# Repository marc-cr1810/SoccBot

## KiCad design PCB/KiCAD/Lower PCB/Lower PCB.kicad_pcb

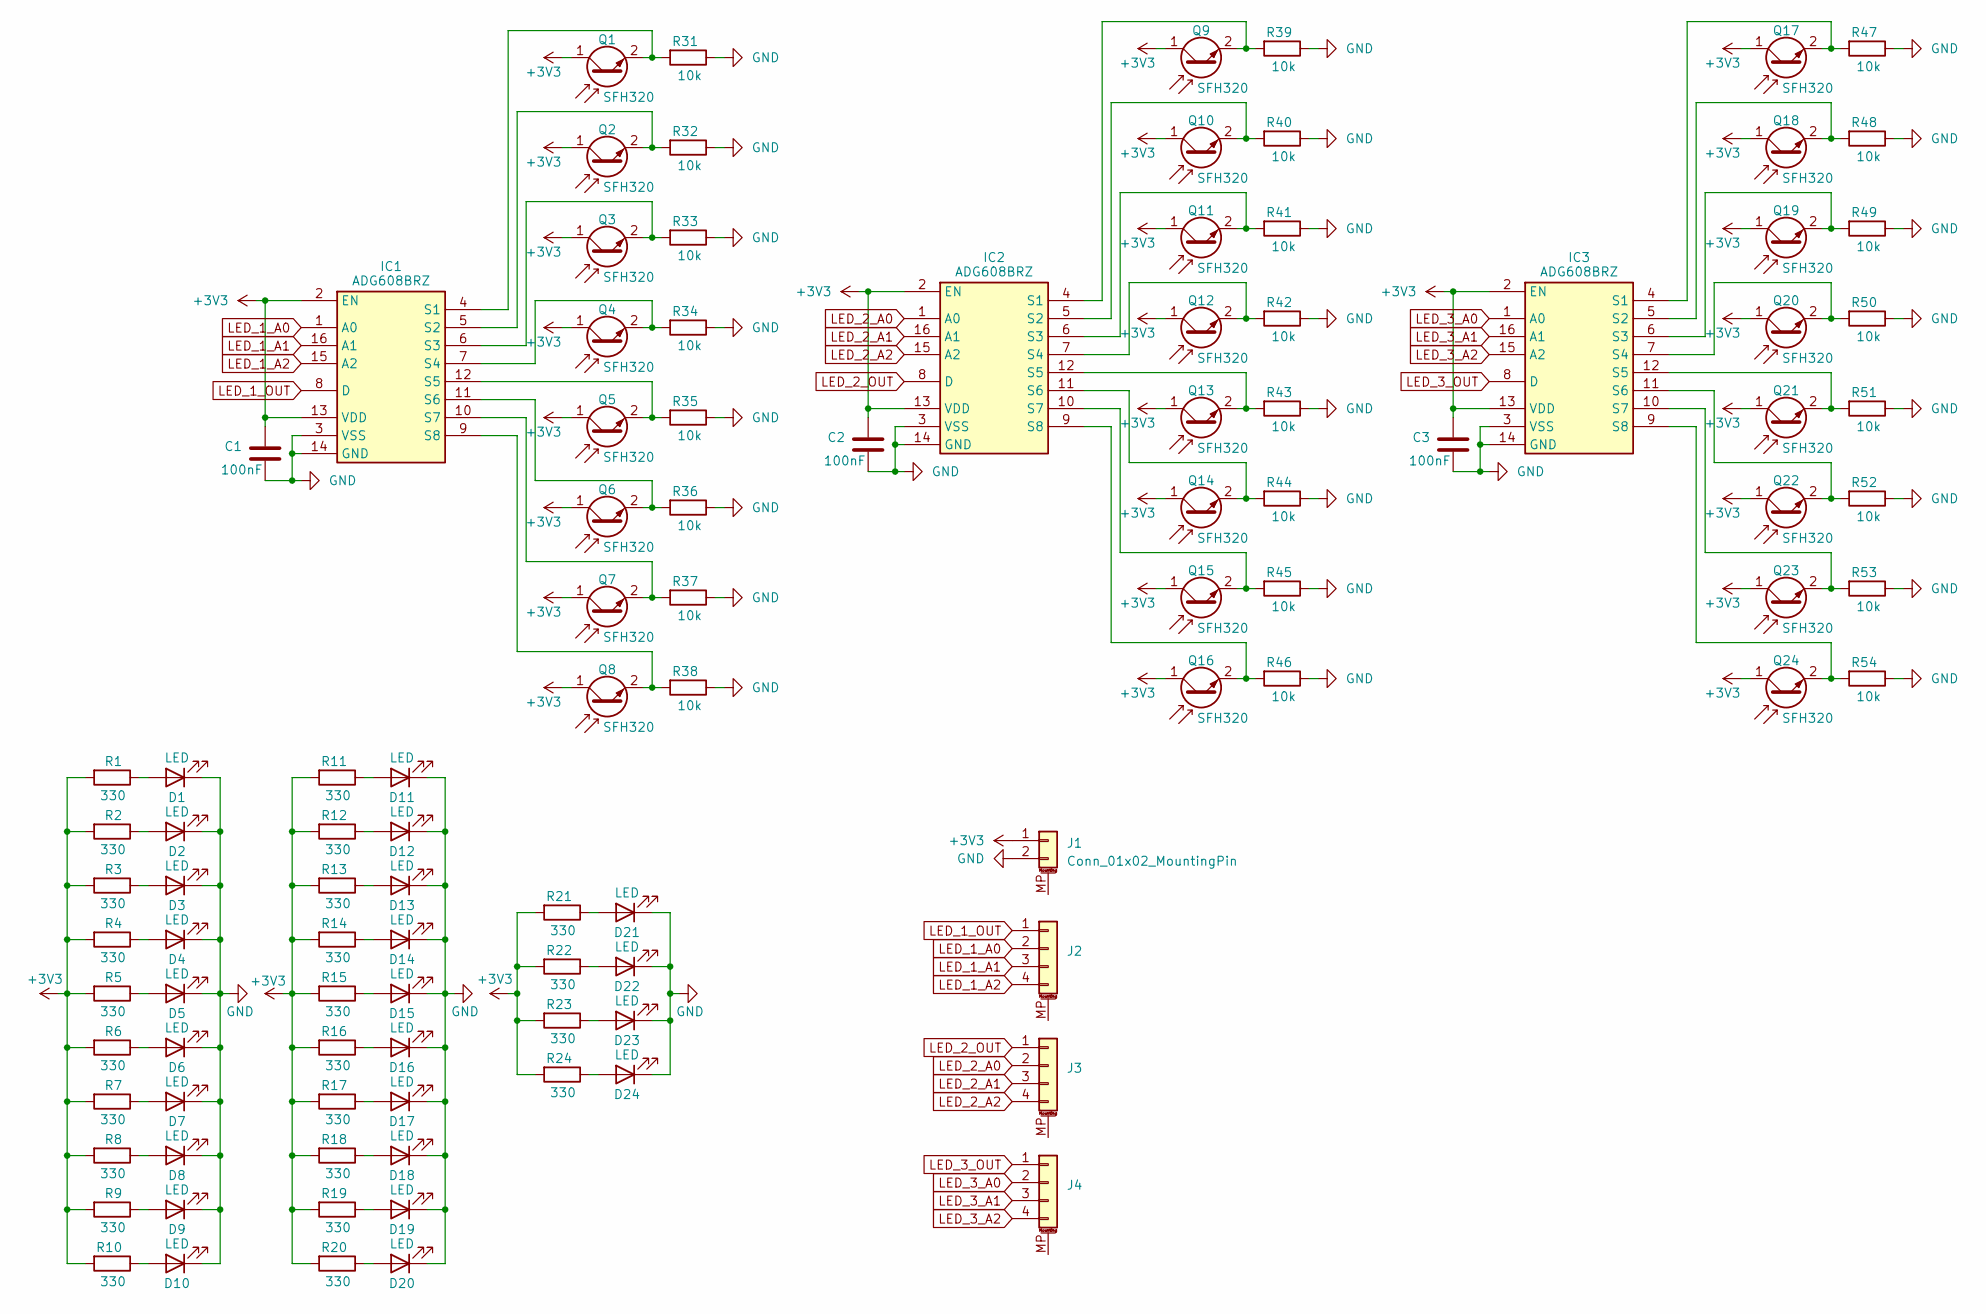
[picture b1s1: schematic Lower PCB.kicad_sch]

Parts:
C1, C2, C3: 100nF; C_0805_2012Metric_Pad1.18x1.45mm_HandSolder
D1, D2, D3, D4, D5, D6, D7, D8, D9, D10, D11, D12, D13, D14, D15, D16, D17, D18, D19, D20, D21, D22, D23, D24: LED; LED_PLCC-2_3.4x3.0mm_KA
IC1, IC2, IC3: ADG608BRZ; SOIC127P600X175-16N; Mouser Part Number 584-ADG608BRZ
J1: Conn_01x02_MountingPin; JST_PH_S2B-PH-SM4-TB_1x02-1MP_P2.00mm_Horizontal
J2, J3, J4: Conn_01x04_MountingPin; JST_PH_S4B-PH-SM4-TB_1x04-1MP_P2.00mm_Horizontal
Q1, Q2, Q3, Q4, Q5, Q6, Q7, Q8, Q9, Q10, Q11, Q12, Q13, Q14, Q15, Q16, Q17, Q18, Q19, Q20, Q21, Q22, Q23, Q24: SFH320; LED_PLCC-2_3.4x3.0mm_KA
R1, R2, R3, R4, R5, R6, R7, R8, R9, R10, R11, R12, R13, R14, R15, R16, R17, R18, R19, R20, R21, R22, R23, R24: 330; R_0805_2012Metric_Pad1.20x1.40mm_HandSolder
R31, R32, R33, R34, R35, R36, R37, R38, R39, R40, R41, R42, R43, R44, R45, R46, R47, R48, R49, R50, R51, R52, R53, R54: 10k; R_0805_2012Metric_Pad1.20x1.40mm_HandSolder

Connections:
+3V3: C1.1, C2.1, C3.1, IC1.2 (EN), IC1.13 (VDD), IC2.2 (EN), IC2.13 (VDD), IC3.2 (EN), IC3.13 (VDD), J1.1, Q1.1 (C), Q2.1 (C), Q3.1 (C), Q4.1 (C), Q5.1 (C), Q6.1 (C), Q7.1 (C), Q8.1 (C), Q9.1 (C), Q10.1 (C), Q11.1 (C), Q12.1 (C), Q13.1 (C), Q14.1 (C), Q15.1 (C), Q16.1 (C), Q17.1 (C), Q18.1 (C), Q19.1 (C), Q20.1 (C), Q21.1 (C), Q22.1 (C), Q23.1 (C), Q24.1 (C), R1.2, R2.2, R3.2, R4.2, R5.2, R6.2, R7.2, R8.2, R9.2, R10.2, R11.2, R12.2, R13.2, R14.2, R15.2, R16.2, R17.2, R18.2, R19.2, R20.2, R21.2, R22.2, R23.2, R24.2
GND: C1.2, C2.2, C3.2, D1.1 (K), D2.1 (K), D3.1 (K), D4.1 (K), D5.1 (K), D6.1 (K), D7.1 (K), D8.1 (K), D9.1 (K), D10.1 (K), D11.1 (K), D12.1 (K), D13.1 (K), D14.1 (K), D15.1 (K), D16.1 (K), D17.1 (K), D18.1 (K), D19.1 (K), D20.1 (K), D21.1 (K), D22.1 (K), D23.1 (K), D24.1 (K), IC1.3 (VSS), IC1.14 (GND), IC2.3 (VSS), IC2.14 (GND), IC3.3 (VSS), IC3.14 (GND), J1.2, R31.1, R32.1, R33.1, R34.1, R35.1, R36.1, R37.1, R38.1, R39.1, R40.1, R41.1, R42.1, R43.1, R44.1, R45.1, R46.1, R47.1, R48.1, R49.1, R50.1, R51.1, R52.1, R53.1, R54.1
LED_1_A0: IC1.1 (A0), J2.2
LED_1_A1: IC1.16 (A1), J2.3
LED_1_A2: IC1.15 (A2), J2.4
LED_1_OUT: IC1.8 (D), J2.1
LED_2_A0: IC2.1 (A0), J3.2
LED_2_A1: IC2.16 (A1), J3.3
LED_2_A2: IC2.15 (A2), J3.4
LED_2_OUT: IC2.8 (D), J3.1
LED_3_A0: IC3.1 (A0), J4.2
LED_3_A1: IC3.16 (A1), J4.3
LED_3_A2: IC3.15 (A2), J4.4
LED_3_OUT: IC3.8 (D), J4.1
unnamed: D1.2 (A), R1.1
unnamed: D2.2 (A), R2.1
unnamed: D3.2 (A), R3.1
unnamed: D4.2 (A), R4.1
unnamed: D5.2 (A), R5.1
unnamed: D6.2 (A), R6.1
unnamed: D7.2 (A), R7.1
unnamed: D8.2 (A), R8.1
unnamed: D9.2 (A), R9.1
unnamed: D10.2 (A), R10.1
unnamed: D11.2 (A), R11.1
unnamed: D12.2 (A), R12.1
unnamed: D13.2 (A), R13.1
unnamed: D14.2 (A), R14.1
unnamed: D15.2 (A), R15.1
unnamed: D16.2 (A), R16.1
unnamed: D17.2 (A), R17.1
unnamed: D18.2 (A), R18.1
unnamed: D19.2 (A), R19.1
unnamed: D20.2 (A), R20.1
unnamed: D21.2 (A), R21.1
unnamed: D22.2 (A), R22.1
unnamed: D23.2 (A), R23.1
unnamed: D24.2 (A), R24.1
unnamed: IC1.4 (S1), Q1.2 (E), R31.2
unnamed: IC1.5 (S2), Q2.2 (E), R32.2
unnamed: IC1.6 (S3), Q3.2 (E), R33.2
unnamed: IC1.7 (S4), Q4.2 (E), R34.2
unnamed: IC1.12 (S5), Q5.2 (E), R35.2
unnamed: IC1.11 (S6), Q6.2 (E), R36.2
unnamed: IC1.10 (S7), Q7.2 (E), R37.2
unnamed: IC1.9 (S8), Q8.2 (E), R38.2
unnamed: IC2.4 (S1), Q9.2 (E), R39.2
unnamed: IC2.5 (S2), Q10.2 (E), R40.2
unnamed: IC2.6 (S3), Q11.2 (E), R41.2
unnamed: IC2.7 (S4), Q12.2 (E), R42.2
unnamed: IC2.12 (S5), Q13.2 (E), R43.2
unnamed: IC2.11 (S6), Q14.2 (E), R44.2
unnamed: IC2.10 (S7), Q15.2 (E), R45.2
unnamed: IC2.9 (S8), Q16.2 (E), R46.2
unnamed: IC3.4 (S1), Q17.2 (E), R47.2
unnamed: IC3.5 (S2), Q18.2 (E), R48.2
unnamed: IC3.6 (S3), Q19.2 (E), R49.2
unnamed: IC3.7 (S4), Q20.2 (E), R50.2
unnamed: IC3.12 (S5), Q21.2 (E), R51.2
unnamed: IC3.11 (S6), Q22.2 (E), R52.2
unnamed: IC3.10 (S7), Q23.2 (E), R53.2
unnamed: IC3.9 (S8), Q24.2 (E), R54.2

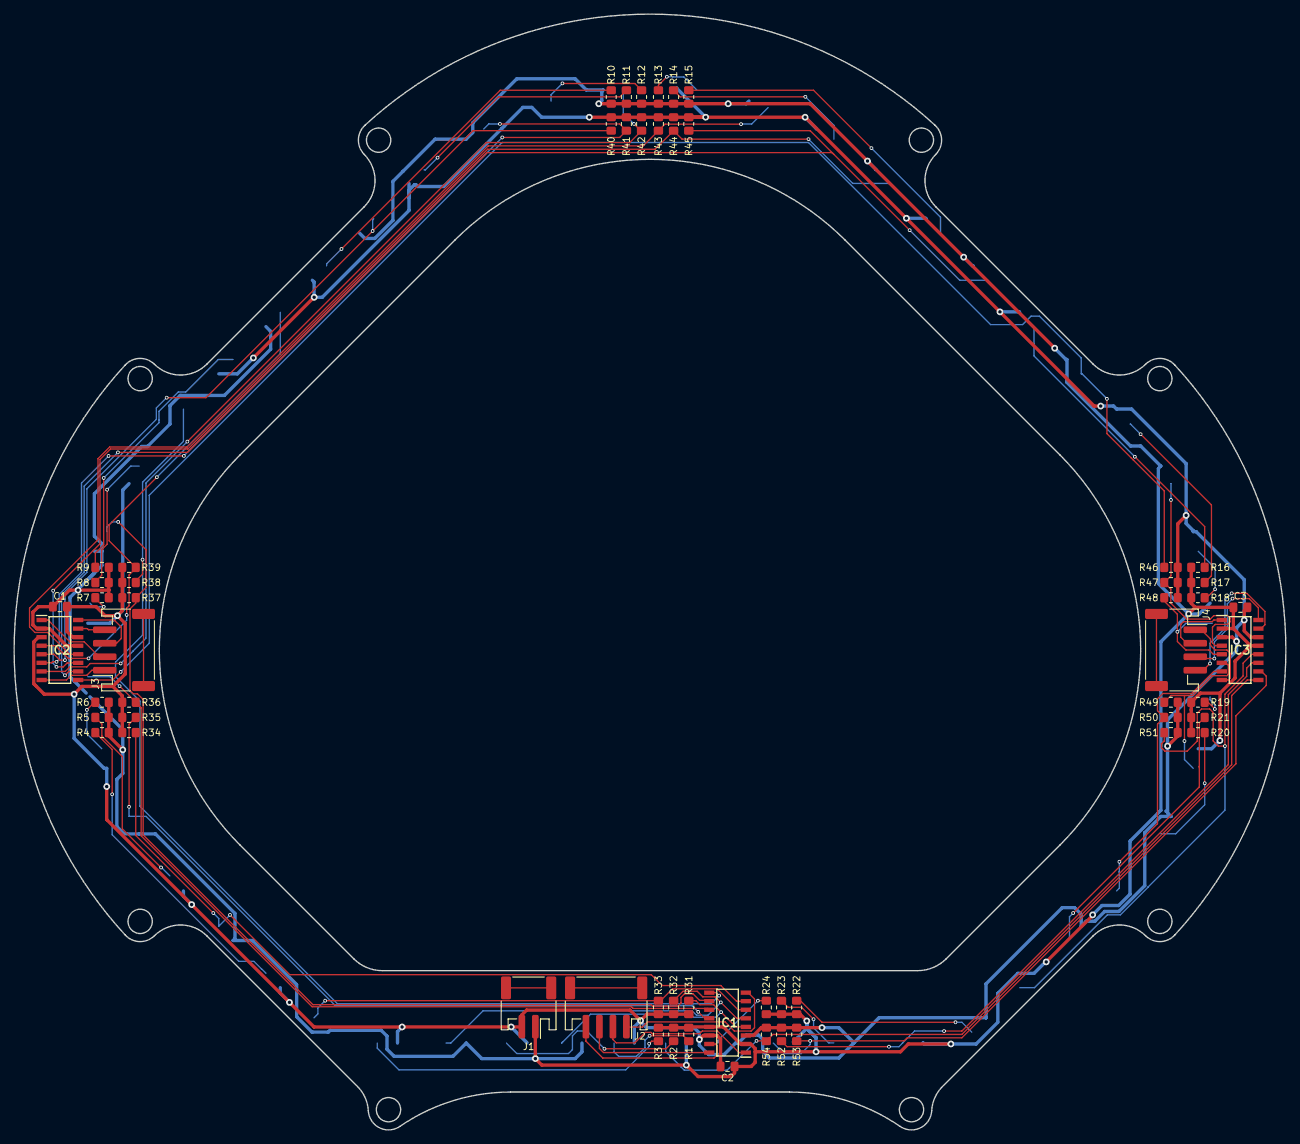
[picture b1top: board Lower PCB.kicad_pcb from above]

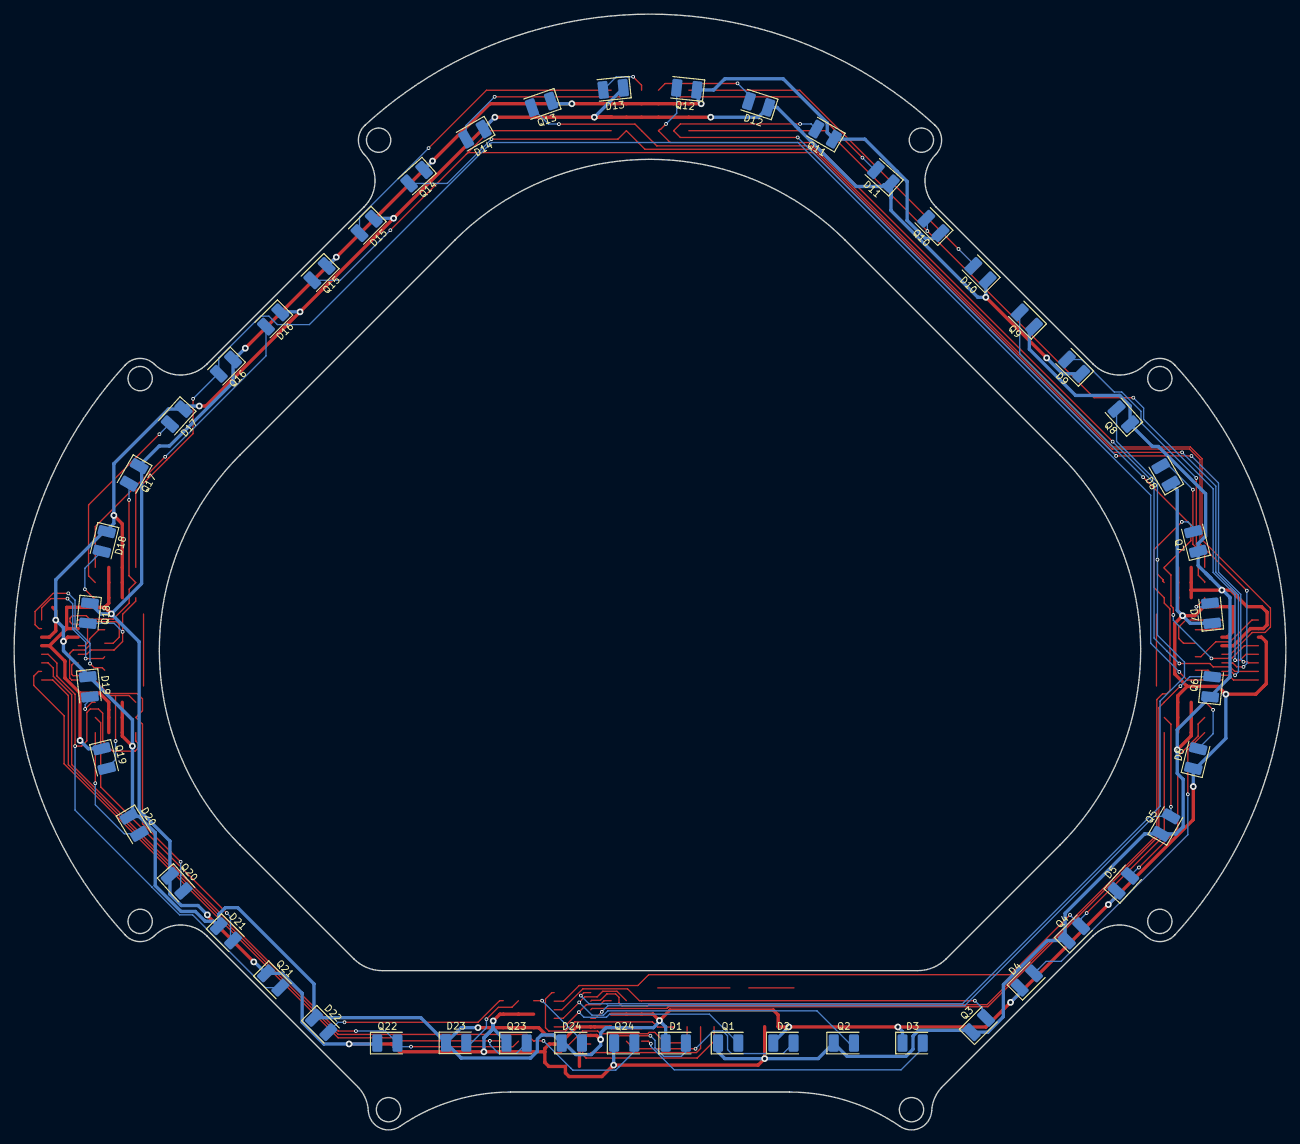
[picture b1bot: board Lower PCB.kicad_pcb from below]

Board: 2 copper layers, 188.6 x 165.4 mm, 106 parts (48 on the bottom side), 62 nets.

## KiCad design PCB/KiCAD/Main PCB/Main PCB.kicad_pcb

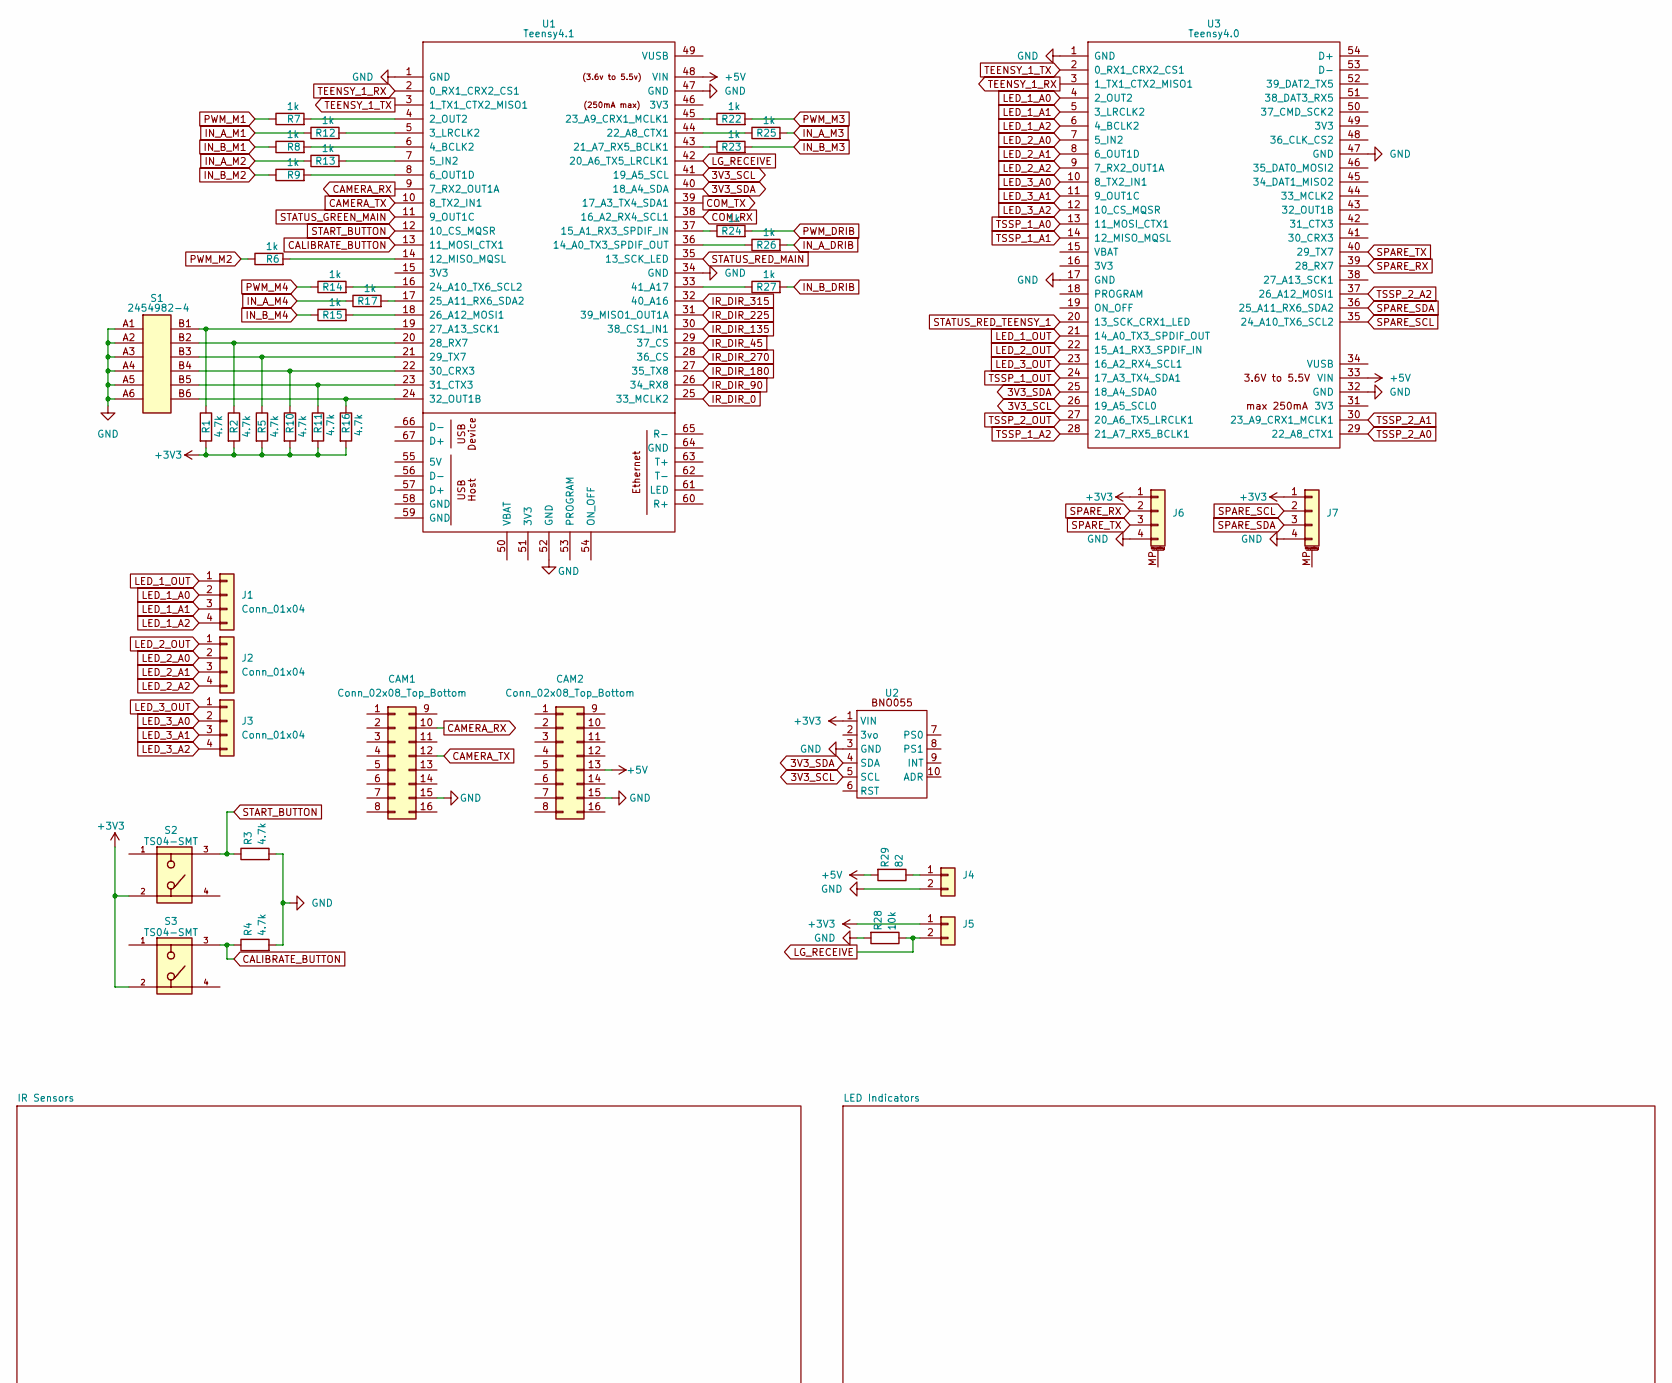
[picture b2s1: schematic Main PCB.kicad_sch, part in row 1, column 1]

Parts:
CAM1, CAM2: Conn_02x08_Top_Bottom; PinSocket_2x08_P2.54mm_Vertical
J1, J2, J3: Conn_01x04; JST_PH_B4B-PH-K_1x04_P2.00mm_Vertical
J4, J5: Conn_01x02; JST_PH_B2B-PH-K_1x02_P2.00mm_Vertical
J6, J7: Conn_01x04_MountingPin; JST_PH_S4B-PH-SM4-TB_1x04-1MP_P2.00mm_Horizontal
R1, R2, R3, R4, R5, R10, R11, R16: 4.7k; R_0805_2012Metric_Pad1.20x1.40mm_HandSolder
R6, R7, R8, R9, R12, R13, R14, R15, R17, R22, R23, R24, R25, R26, R27: 1k; R_0805_2012Metric_Pad1.20x1.40mm_HandSolder
R28: 10k; R_0805_2012Metric_Pad1.20x1.40mm_HandSolder
R29: 82; R_0805_2012Metric_Pad1.20x1.40mm_HandSolder
S1: 2454982-4; DIP_6_SWITCH_THT; Mouser Part Number 655-2454982-4
S2, S3: TS04-SMT; SW_TS04-66-70-BK-260-SMT; PARTREV 1.0
U1: Teensy4.1; Teensy41
U2: BNO055
U3: Teensy4.0; Teensy40

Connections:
3V3_SCL: U1.41 (19_A5_SCL), U2.5 (SCL), U3.26 (19_A5_SCL0)
3V3_SDA: U1.40 (18_A4_SDA), U2.4 (SDA), U3.25 (18_A4_SDA0)
+3V3: J5.1, J6.1, J7.1, R1.2, R2.2, R5.2, R10.2, R11.2, R16.2, S2.2, S3.2, U2.1 (VIN); also elsewhere on the board
+5V: CAM2.13, R29.2, U1.48 (VIN), U3.33 (VIN); also elsewhere on the board
CALIBRATE_BUTTON: R4.1, S3.3, U1.13 (11_MOSI_CTX1)
CAMERA_RX: CAM1.10, U1.9 (7_RX2_OUT1A)
CAMERA_TX: CAM1.12, U1.10 (8_TX2_IN1)
COM_RX: U1.38 (16_A2_RX4_SCL1); also elsewhere on the board
COM_TX: U1.39 (17_A3_TX4_SDA1); also elsewhere on the board
GND: CAM1.15, CAM2.15, J4.2, J6.4, J7.4, R3.2, R4.2, R28.2, S1.A1, S1.A2, S1.A3, S1.A4, S1.A5, S1.A6, U1.1 (GND), U1.34 (GND), U1.47 (GND), U1.52 (GND), U2.3 (GND), U3.1 (GND), U3.17 (GND), U3.32 (GND), U3.47 (GND); also elsewhere on the board
IN_A_DRIB: R26.2; also elsewhere on the board
IN_A_M1: R12.1; also elsewhere on the board
IN_A_M2: R13.1; also elsewhere on the board
IN_A_M3: R25.2; also elsewhere on the board
IN_A_M4: R17.1; also elsewhere on the board
IN_B_DRIB: R27.2; also elsewhere on the board
IN_B_M1: R8.1; also elsewhere on the board
IN_B_M2: R9.1; also elsewhere on the board
IN_B_M3: R23.2; also elsewhere on the board
IN_B_M4: R15.1; also elsewhere on the board
IR_DIR_0: U1.25 (33_MCLK2); also elsewhere on the board
IR_DIR_45: U1.29 (37_CS); also elsewhere on the board
IR_DIR_90: U1.26 (34_RX8); also elsewhere on the board
IR_DIR_135: U1.30 (38_CS1_IN1); also elsewhere on the board
IR_DIR_180: U1.27 (35_TX8); also elsewhere on the board
IR_DIR_225: U1.31 (39_MISO1_OUT1A); also elsewhere on the board
IR_DIR_270: U1.28 (36_CS); also elsewhere on the board
IR_DIR_315: U1.32 (40_A16); also elsewhere on the board
LED_1_A0: J1.2, U3.4 (2_OUT2)
LED_1_A1: J1.3, U3.5 (3_LRCLK2)
LED_1_A2: J1.4, U3.6 (4_BCLK2)
LED_1_OUT: J1.1, U3.21 (14_A0_TX3_SPDIF_OUT)
LED_2_A0: J2.2, U3.7 (5_IN2)
LED_2_A1: J2.3, U3.8 (6_OUT1D)
LED_2_A2: J2.4, U3.9 (7_RX2_OUT1A)
LED_2_OUT: J2.1, U3.22 (15_A1_RX3_SPDIF_IN)
LED_3_A0: J3.2, U3.10 (8_TX2_IN1)
LED_3_A1: J3.3, U3.11 (9_OUT1C)
LED_3_A2: J3.4, U3.12 (10_CS_MQSR)
LED_3_OUT: J3.1, U3.23 (16_A2_RX4_SCL1)
LG_RECEIVE: J5.2, R28.1, U1.42 (20_A6_TX5_LRCLK1)
unnamed: J4.1, R29.1
unnamed: R7.2, U1.4 (2_OUT2)
unnamed: R12.2, U1.5 (3_LRCLK2)
unnamed: R8.2, U1.6 (4_BCLK2)
unnamed: R13.2, U1.7 (5_IN2)
unnamed: R9.2, U1.8 (6_OUT1D)
unnamed: R6.2, U1.14 (12_MISO_MQSL)
unnamed: R26.1, U1.36 (14_A0_TX3_SPDIF_OUT)
unnamed: R24.1, U1.37 (15_A1_RX3_SPDIF_IN)
unnamed: R23.1, U1.43 (21_A7_RX5_BCLK1)
unnamed: R25.1, U1.44 (22_A8_CTX1)
unnamed: R22.1, U1.45 (23_A9_CRX1_MCLK1)
unnamed: R14.2, U1.16 (24_A10_TX6_SCL2)
unnamed: R17.2, U1.17 (25_A11_RX6_SDA2)
unnamed: R15.2, U1.18 (26_A12_MOSI1)
unnamed: R1.1, S1.B1, U1.19 (27_A13_SCK1)
unnamed: R2.1, S1.B2, U1.20 (28_RX7)
unnamed: R5.1, S1.B3, U1.21 (29_TX7)
unnamed: R10.1, S1.B4, U1.22 (30_CRX3)
unnamed: R11.1, S1.B5, U1.23 (31_CTX3)
unnamed: R16.1, S1.B6, U1.24 (32_OUT1B)
unnamed: R27.1, U1.33 (41_A17)
PWM_DRIB: R24.2; also elsewhere on the board
PWM_M1: R7.1; also elsewhere on the board
PWM_M2: R6.1; also elsewhere on the board
PWM_M3: R22.2; also elsewhere on the board
PWM_M4: R14.1; also elsewhere on the board
SPARE_RX: J6.2, U3.39 (28_RX7)
SPARE_SCL: J7.2, U3.35 (24_A10_TX6_SCL2)
SPARE_SDA: J7.3, U3.36 (25_A11_RX6_SDA2)
SPARE_TX: J6.3, U3.40 (29_TX7)
START_BUTTON: R3.1, S2.3, U1.12 (10_CS_MQSR)
STATUS_GREEN_MAIN: U1.11 (9_OUT1C); also elsewhere on the board
STATUS_RED_MAIN: U1.35 (13_SCK_LED); also elsewhere on the board
STATUS_RED_TEENSY_1: U3.20 (13_SCK_CRX1_LED)
TEENSY_1_RX: U1.2 (0_RX1_CRX2_CS1), U3.3 (1_TX1_CTX2_MISO1)
TEENSY_1_TX: U1.3 (1_TX1_CTX2_MISO1), U3.2 (0_RX1_CRX2_CS1)
TSSP_1_A0: U3.13 (11_MOSI_CTX1); also elsewhere on the board
TSSP_1_A1: U3.14 (12_MISO_MQSL); also elsewhere on the board
TSSP_1_A2: U3.28 (21_A7_RX5_BCLK1); also elsewhere on the board
TSSP_1_OUT: U3.24 (17_A3_TX4_SDA1); also elsewhere on the board
TSSP_2_A0: U3.29 (22_A8_CTX1); also elsewhere on the board
TSSP_2_A1: U3.30 (23_A9_CRX1_MCLK1); also elsewhere on the board
TSSP_2_A2: U3.37 (26_A12_MOSI1); also elsewhere on the board
TSSP_2_OUT: U3.27 (20_A6_TX5_LRCLK1); also elsewhere on the board

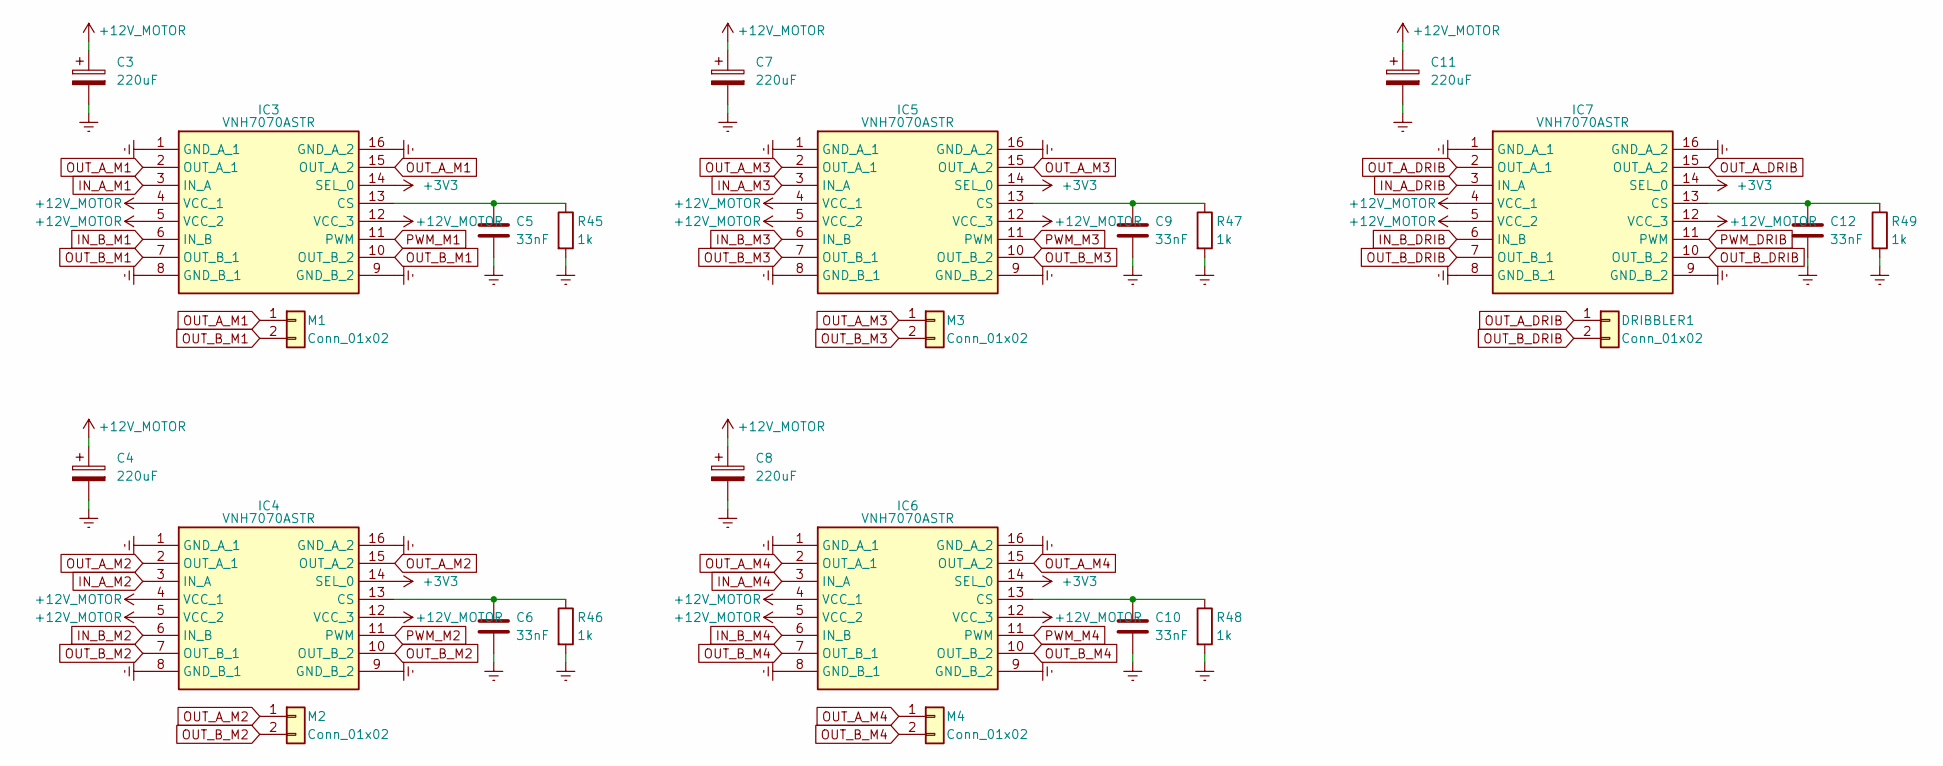
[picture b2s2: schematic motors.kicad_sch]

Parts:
C3, C4, C7, C8, C11: 220uF; CP_Elec_10x10
C5, C6, C9, C10, C12: 33nF; C_0805_2012Metric_Pad1.18x1.45mm_HandSolder
DRIBBLER1: Conn_01x02; JST_VH_B2P-VH-B_1x02_P3.96mm_Vertical
IC3, IC4, IC5, IC6, IC7: VNH7070ASTR; SOIC127P600X175-16N; Mouser Part Number 511-VNH7070ASTR
M1, M2, M3, M4: Conn_01x02; JST_VH_B2P-VH-B_1x02_P3.96mm_Vertical
R45, R46, R47, R48, R49: 1k; R_0805_2012Metric_Pad1.20x1.40mm_HandSolder

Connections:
+3V3: IC3.14 (SEL_0), IC4.14 (SEL_0), IC5.14 (SEL_0), IC6.14 (SEL_0), IC7.14 (SEL_0); also elsewhere on the board
+12V_MOTOR: C3.1, C4.1, C7.1, C8.1, C11.1, IC3.4 (VCC_1), IC3.5 (VCC_2), IC3.12 (VCC_3), IC4.4 (VCC_1), IC4.5 (VCC_2), IC4.12 (VCC_3), IC5.4 (VCC_1), IC5.5 (VCC_2), IC5.12 (VCC_3), IC6.4 (VCC_1), IC6.5 (VCC_2), IC6.12 (VCC_3), IC7.4 (VCC_1), IC7.5 (VCC_2), IC7.12 (VCC_3); also elsewhere on the board
GND: C3.2, C4.2, C5.2, C6.2, C7.2, C8.2, C9.2, C10.2, C11.2, C12.2, IC3.1 (GND_A_1), IC3.8 (GND_B_1), IC3.9 (GND_B_2), IC3.16 (GND_A_2), IC4.1 (GND_A_1), IC4.8 (GND_B_1), IC4.9 (GND_B_2), IC4.16 (GND_A_2), IC5.1 (GND_A_1), IC5.8 (GND_B_1), IC5.9 (GND_B_2), IC5.16 (GND_A_2), IC6.1 (GND_A_1), IC6.8 (GND_B_1), IC6.9 (GND_B_2), IC6.16 (GND_A_2), IC7.1 (GND_A_1), IC7.8 (GND_B_1), IC7.9 (GND_B_2), IC7.16 (GND_A_2), R45.2, R46.2, R47.2, R48.2, R49.2; also elsewhere on the board
IN_A_DRIB: IC7.3 (IN_A); also elsewhere on the board
IN_A_M1: IC3.3 (IN_A); also elsewhere on the board
IN_A_M2: IC4.3 (IN_A); also elsewhere on the board
IN_A_M3: IC5.3 (IN_A); also elsewhere on the board
IN_A_M4: IC6.3 (IN_A); also elsewhere on the board
IN_B_DRIB: IC7.6 (IN_B); also elsewhere on the board
IN_B_M1: IC3.6 (IN_B); also elsewhere on the board
IN_B_M2: IC4.6 (IN_B); also elsewhere on the board
IN_B_M3: IC5.6 (IN_B); also elsewhere on the board
IN_B_M4: IC6.6 (IN_B); also elsewhere on the board
unnamed: C5.1, IC3.13 (CS), R45.1
unnamed: C6.1, IC4.13 (CS), R46.1
unnamed: C9.1, IC5.13 (CS), R47.1
unnamed: C10.1, IC6.13 (CS), R48.1
unnamed: C12.1, IC7.13 (CS), R49.1
OUT_A_DRIB: DRIBBLER1.1, IC7.2 (OUT_A_1), IC7.15 (OUT_A_2)
OUT_A_M1: IC3.2 (OUT_A_1), IC3.15 (OUT_A_2), M1.1
OUT_A_M2: IC4.2 (OUT_A_1), IC4.15 (OUT_A_2), M2.1
OUT_A_M3: IC5.2 (OUT_A_1), IC5.15 (OUT_A_2), M3.1
OUT_A_M4: IC6.2 (OUT_A_1), IC6.15 (OUT_A_2), M4.1
OUT_B_DRIB: DRIBBLER1.2, IC7.7 (OUT_B_1), IC7.10 (OUT_B_2)
OUT_B_M1: IC3.7 (OUT_B_1), IC3.10 (OUT_B_2), M1.2
OUT_B_M2: IC4.7 (OUT_B_1), IC4.10 (OUT_B_2), M2.2
OUT_B_M3: IC5.7 (OUT_B_1), IC5.10 (OUT_B_2), M3.2
OUT_B_M4: IC6.7 (OUT_B_1), IC6.10 (OUT_B_2), M4.2
PWM_DRIB: IC7.11 (PWM); also elsewhere on the board
PWM_M1: IC3.11 (PWM); also elsewhere on the board
PWM_M2: IC4.11 (PWM); also elsewhere on the board
PWM_M3: IC5.11 (PWM); also elsewhere on the board
PWM_M4: IC6.11 (PWM); also elsewhere on the board

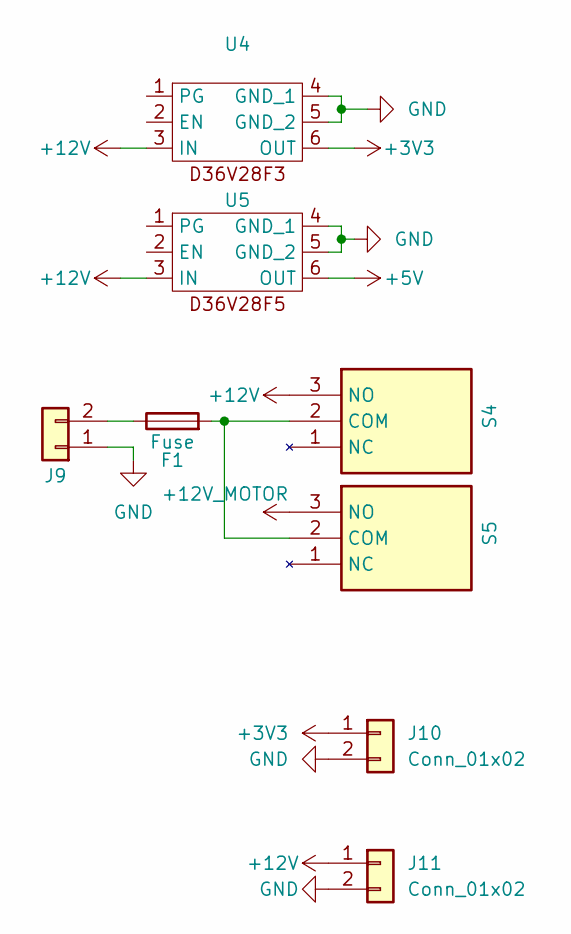
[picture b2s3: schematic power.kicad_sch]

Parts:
F1: Fuse; Fuseholder_Blade_Mini_Keystone_3568
J9: Conn_01x02; AMASS_XT60-M_1x02_P7.20mm_Vertical
J10: Conn_01x02; JST_PH_B2B-PH-K_1x02_P2.00mm_Vertical
J11: Conn_01x02; AMASS_XT30U-M_1x02_P5.0mm_Vertical
S4, S5: 1101M2S3CGE2; Mouser Part Number 611-1101M2S3CGE2
U4: D36V28F3
U5: D36V28F5

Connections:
+3V3: J10.1, U4.6 (OUT); also elsewhere on the board
+5V: U5.6 (OUT); also elsewhere on the board
+12V: J11.1, S4.3 (NO), U4.3 (IN), U5.3 (IN)
+12V_MOTOR: S5.3 (NO); also elsewhere on the board
GND: J9.1, J10.2, J11.2, U4.4 (GND_1), U4.5 (GND_2), U5.4 (GND_1), U5.5 (GND_2); also elsewhere on the board
unnamed: F1.1, J9.2
unnamed: F1.2, S4.2 (COM), S5.2 (COM)

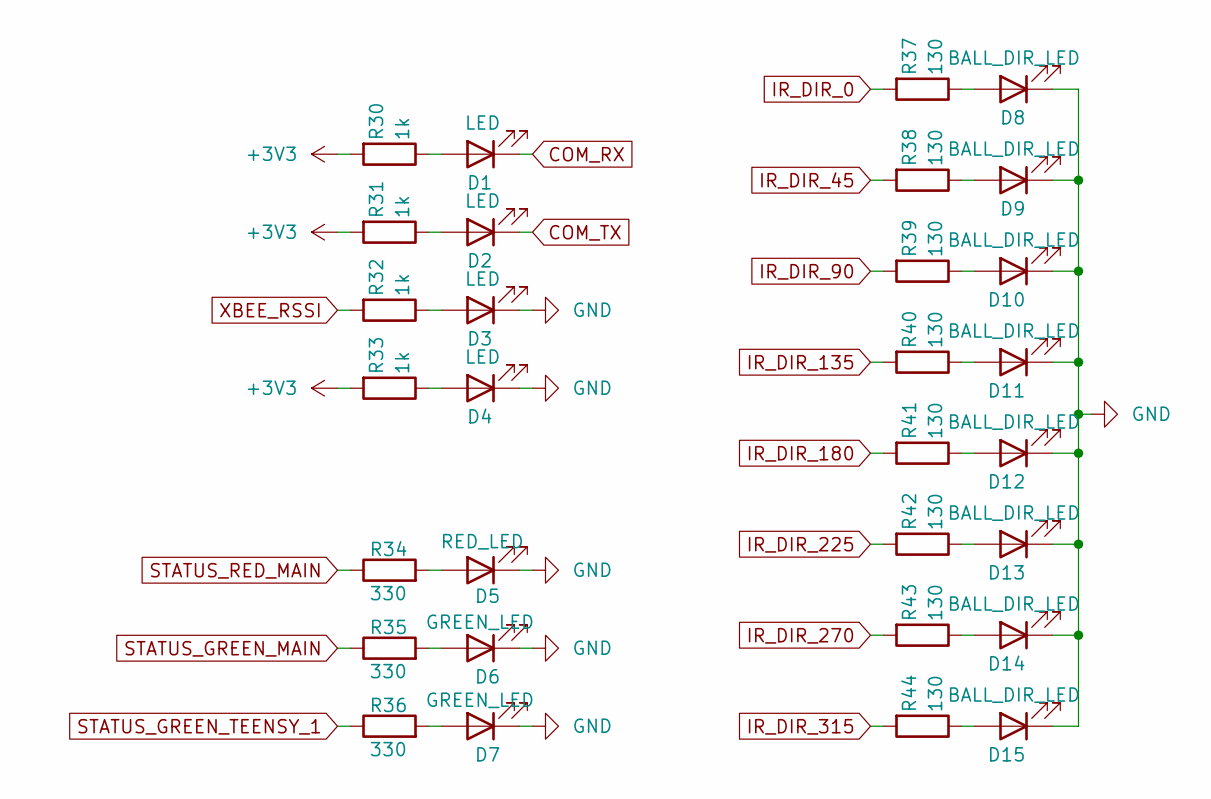
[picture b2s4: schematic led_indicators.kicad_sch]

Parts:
D1, D2, D3, D4: LED; LED_0805_2012Metric_Pad1.15x1.40mm_HandSolder
D5: RED_LED; LED_0805_2012Metric_Pad1.15x1.40mm_HandSolder
D6, D7: GREEN_LED; LED_0805_2012Metric_Pad1.15x1.40mm_HandSolder
D8, D9, D10, D11, D12, D13, D14, D15: BALL_DIR_LED; LED_0805_2012Metric_Pad1.15x1.40mm_HandSolder
R30, R31, R32, R33: 1k; R_0805_2012Metric_Pad1.20x1.40mm_HandSolder
R34, R35, R36: 330; R_0805_2012Metric_Pad1.20x1.40mm_HandSolder
R37, R38, R39, R40, R41, R42, R43, R44: 130; R_0805_2012Metric_Pad1.20x1.40mm_HandSolder

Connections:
+3V3: R30.2, R31.2, R33.2; also elsewhere on the board
COM_RX: D1.1 (K); also elsewhere on the board
COM_TX: D2.1 (K); also elsewhere on the board
GND: D3.1 (K), D4.1 (K), D5.1 (K), D6.1 (K), D7.1 (K), D8.1 (K), D9.1 (K), D10.1 (K), D11.1 (K), D12.1 (K), D13.1 (K), D14.1 (K), D15.1 (K); also elsewhere on the board
IR_DIR_0: R37.2; also elsewhere on the board
IR_DIR_45: R38.2; also elsewhere on the board
IR_DIR_90: R39.2; also elsewhere on the board
IR_DIR_135: R40.2; also elsewhere on the board
IR_DIR_180: R41.2; also elsewhere on the board
IR_DIR_225: R42.2; also elsewhere on the board
IR_DIR_270: R43.2; also elsewhere on the board
IR_DIR_315: R44.2; also elsewhere on the board
unnamed: D1.2 (A), R30.1
unnamed: D2.2 (A), R31.1
unnamed: D3.2 (A), R32.1
unnamed: D4.2 (A), R33.1
unnamed: D5.2 (A), R34.2
unnamed: D6.2 (A), R35.2
unnamed: D7.2 (A), R36.2
unnamed: D8.2 (A), R37.1
unnamed: D9.2 (A), R38.1
unnamed: D10.2 (A), R39.1
unnamed: D11.2 (A), R40.1
unnamed: D12.2 (A), R41.1
unnamed: D13.2 (A), R42.1
unnamed: D14.2 (A), R43.1
unnamed: D15.2 (A), R44.1
STATUS_GREEN_MAIN: R35.1; also elsewhere on the board
STATUS_GREEN_TEENSY_1: R36.1
STATUS_RED_MAIN: R34.1; also elsewhere on the board
XBEE_RSSI: R32.2; also elsewhere on the board

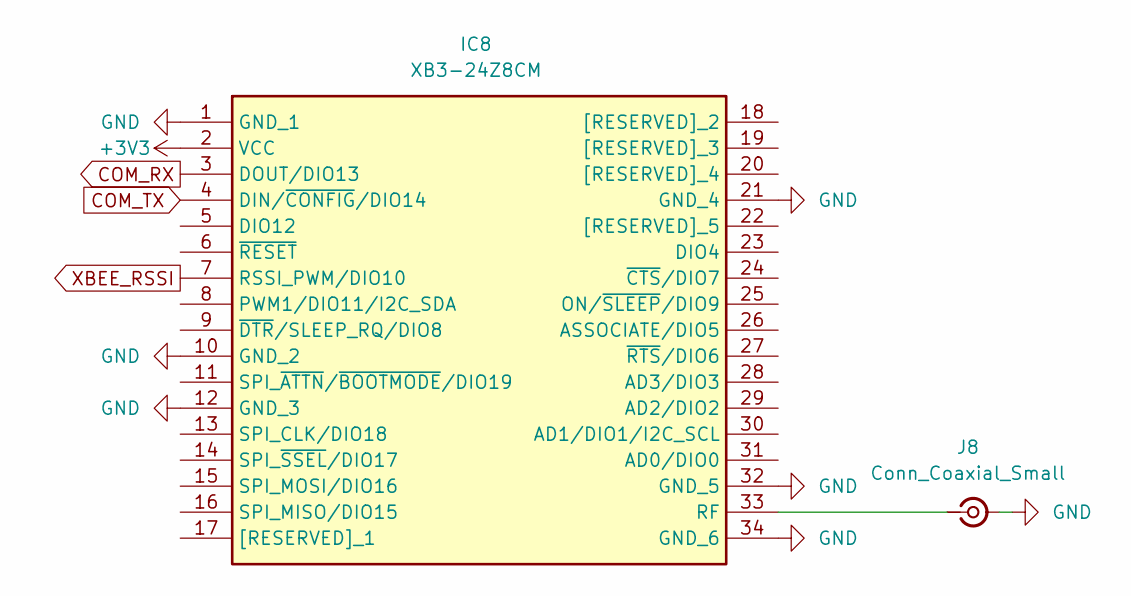
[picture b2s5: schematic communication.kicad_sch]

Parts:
IC8: XB3-24Z8CM; XB324Z8CMJ; Mouser Part Number 888-XB3-24Z8CM
J8: Conn_Coaxial_Small; U.FL_Hirose_U.FL-R-SMT-1_Vertical

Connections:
+3V3: IC8.2 (VCC); also elsewhere on the board
COM_RX: IC8.3 (DOUT/DIO13); also elsewhere on the board
COM_TX: IC8.4 (DIN/~CONFIG/DIO14); also elsewhere on the board
GND: IC8.1 (GND_1), IC8.10 (GND_2), IC8.12 (GND_3), IC8.21 (GND_4), IC8.32 (GND_5), IC8.34 (GND_6), J8.2 (Ext); also elsewhere on the board
unnamed: IC8.33 (RF), J8.1 (In)
XBEE_RSSI: IC8.7 (RSSI_PWM/DIO10); also elsewhere on the board

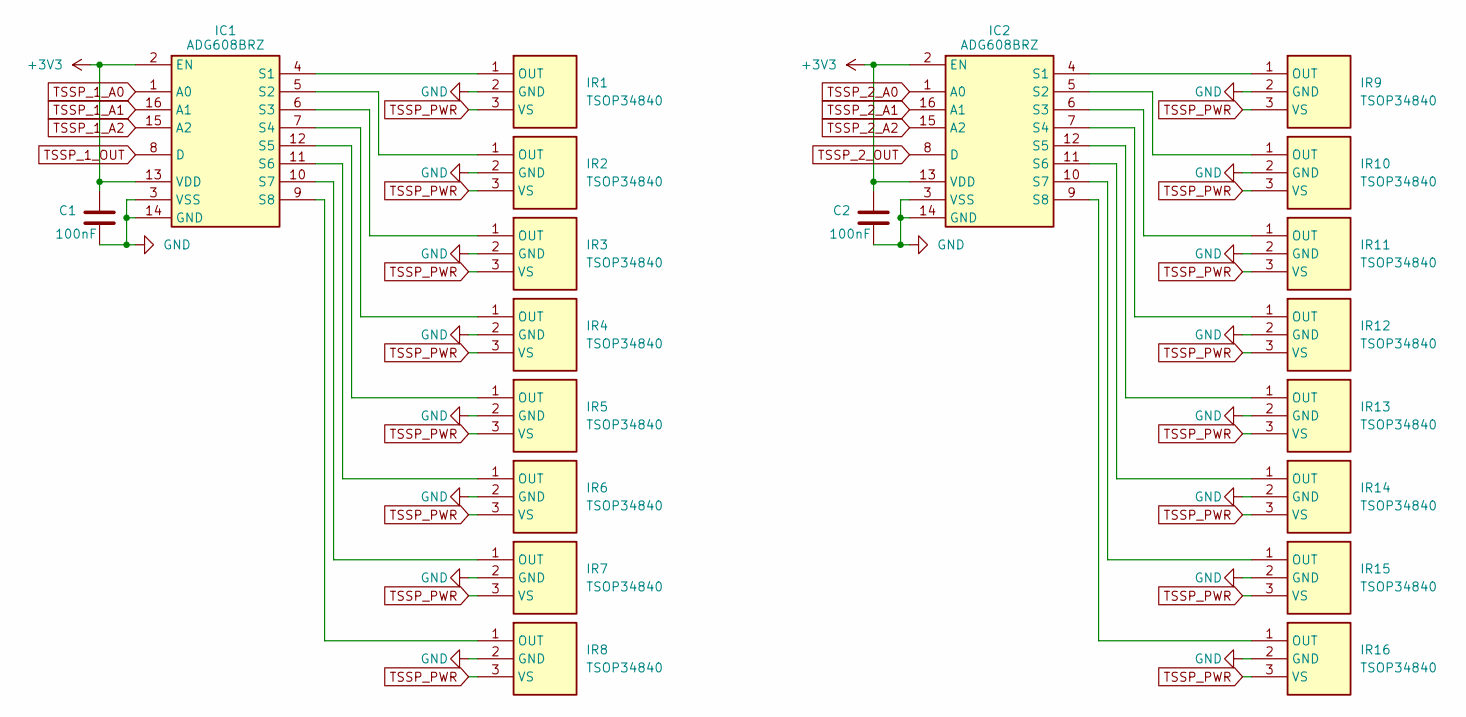
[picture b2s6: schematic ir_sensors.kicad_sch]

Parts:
C1, C2: 100nF; C_0805_2012Metric_Pad1.18x1.45mm_HandSolder
IC1, IC2: ADG608BRZ; SOIC127P600X175-16N; Mouser Part Number 584-ADG608BRZ
IR1, IR2, IR3, IR4, IR5, IR6, IR7, IR8, IR9, IR10, IR11, IR12, IR13, IR14, IR15, IR16: TSOP34840; TSSP4038; Mouser Part Number 782-TSSP4038

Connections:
+3V3: C1.1, C2.1, IC1.2 (EN), IC1.13 (VDD), IC2.2 (EN), IC2.13 (VDD); also elsewhere on the board
GND: C1.2, C2.2, IC1.3 (VSS), IC1.14 (GND), IC2.3 (VSS), IC2.14 (GND), IR1.2 (GND), IR2.2 (GND), IR3.2 (GND), IR4.2 (GND), IR5.2 (GND), IR6.2 (GND), IR7.2 (GND), IR8.2 (GND), IR9.2 (GND), IR10.2 (GND), IR11.2 (GND), IR12.2 (GND), IR13.2 (GND), IR14.2 (GND), IR15.2 (GND), IR16.2 (GND); also elsewhere on the board
unnamed: IC1.4 (S1), IR1.1 (OUT)
unnamed: IC1.5 (S2), IR2.1 (OUT)
unnamed: IC1.6 (S3), IR3.1 (OUT)
unnamed: IC1.7 (S4), IR4.1 (OUT)
unnamed: IC1.12 (S5), IR5.1 (OUT)
unnamed: IC1.11 (S6), IR6.1 (OUT)
unnamed: IC1.10 (S7), IR7.1 (OUT)
unnamed: IC1.9 (S8), IR8.1 (OUT)
unnamed: IC2.4 (S1), IR9.1 (OUT)
unnamed: IC2.5 (S2), IR10.1 (OUT)
unnamed: IC2.6 (S3), IR11.1 (OUT)
unnamed: IC2.7 (S4), IR12.1 (OUT)
unnamed: IC2.12 (S5), IR13.1 (OUT)
unnamed: IC2.11 (S6), IR14.1 (OUT)
unnamed: IC2.10 (S7), IR15.1 (OUT)
unnamed: IC2.9 (S8), IR16.1 (OUT)
TSSP_1_A0: IC1.1 (A0); also elsewhere on the board
TSSP_1_A1: IC1.16 (A1); also elsewhere on the board
TSSP_1_A2: IC1.15 (A2); also elsewhere on the board
TSSP_1_OUT: IC1.8 (D); also elsewhere on the board
TSSP_2_A0: IC2.1 (A0); also elsewhere on the board
TSSP_2_A1: IC2.16 (A1); also elsewhere on the board
TSSP_2_A2: IC2.15 (A2); also elsewhere on the board
TSSP_2_OUT: IC2.8 (D); also elsewhere on the board
TSSP_PWR: IR1.3 (VS), IR2.3 (VS), IR3.3 (VS), IR4.3 (VS), IR5.3 (VS), IR6.3 (VS), IR7.3 (VS), IR8.3 (VS), IR9.3 (VS), IR10.3 (VS), IR11.3 (VS), IR12.3 (VS), IR13.3 (VS), IR14.3 (VS), IR15.3 (VS), IR16.3 (VS)
